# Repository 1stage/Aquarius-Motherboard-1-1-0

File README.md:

# Aquarius Motherboard 1-1-0
Aquarius Motherboard 1-1-0 - Rev C

by Sean P. Harrington, sph@1stage.com, http://aquarius.1stage.com, Mack Wharton, aquarius@mack.je, http://aquarius.je
 
## Background
In general, the Aquarius hardware is fairly hardy. Few of the parts go bad, and the system just works, even when stored in harsh or unforgiving environments. Add to that the poor reception the computer had during its brief, 3-4 month sales window in 1983, and there is no REAL reason most people would be interested. But the Mattel Aquarius Computer was the first computer I ever owned. I learned first hand how to program in BASIC, and then how to hack together an audio cable to save those programs to my inexpensive Radio Shack cassette player. However I quickly grew out of it's limited functionality and moved on to a Commodore 64, and then an Apple Macintosh SE, and then Mac II, and then various Windows PCs. It wasn't until Summer of 2019 that I started getting back into retro computers, and it was the pang of guilt I felt in abandoning my first Aquarius that brought me back in.

## Purpose
The purpose of this project is to document and recreate the original Aquarius computer motherboard. This is a like-for-like replacement, and should fit in perfectly in place of the old motherboard. This baseline can be used by other enthusiasts (though we are few and far between) as a starting point for creating new modifications to the system, such as adding a composite video adapter (which I've done) to replace the stock RF modulator, or adding more modern components to "future proof" the system.

Additionally, there was a need to update and correct the "MEKO" schematic from 1986. It was drawn from the PAL board, and values for various components seemed to differ from what was commonly manufactured. From these new schematics, users are welcome to adapt and integrate their own ideas, OR to recreate the system in their eCAD program of choice.

## Caveats
* Some fixes to the stock board were made:
  * The .1uF capacitor that was bodged under U6 has been given a proper set of pads beside U6.
  * Silkscreens were added, with all components being identified. Unfortunately, due to the poor quality of original Radofin documents on the Internet, I had to take a stance and perform a re-number of components, particularly resistors and capacitors. In some cases, these won't match original numbers, but every effort was made to get them as close as possible.
  * Both the PAL-only and NTSC-only components are marked, but only the components for the version being built should be used.
  * As much as possible, original trace paths were recreated (particularly CPU to expansion port), but the traces have been reduced to a 20 mil width on most signals, with all GND and power paths increased to 32 mil width.
  * GND pins now have thermal pads to make soldering and desoldering easier.
* The libraries within the Eagle folder are a mess. I apologize. The board uses a combination of the standard Eagle libraries, some copied/modified versions of those, and some of my own items. I'll eventually try to consolidate them into a single library file. Again, apologies.
* This design was taken from the NTSC version of the Aquarius Motherboard, Radofin part number 5931-4229 A. The values for all components are derived from the NTSC version, and where practical, PAL component values are noted on the schematic. As such, the "part number" embossed on these designs uses 5931-4229 AC to differentiate.
* The schematic does it's best to identify differences between the NTSC and PAL versions, usually with dashed lines surrounding the differences.

## FAQs
* Will these boards be available for sale?
  * https://www.pcbway.com/project/shareproject/Aquarius_Computer_Motherboard_v1_1_0_Rev_C.html
* Can I manufacture and sell the boards myself?
  * Sure, but see the section below on why this is more for SERIOUS hackers than casual users.
* Can you build me a new Aquarius with this PCB?
  * No. I have way too many projects at this time. Also, cost of the components ($$) and my time testing and assembling ($$$) would make this MANY times more expensive than buying a used Aquarius off of eBay.
* Can I build my own, brand new Aquarius computer with this PCB?
  * Realistically, no. There are a handful of custom components (bespoke, we like to say) that ONLY exist in the Aquarius computer... the PLA1 and PLA2, some line filters, and a variable inductor... each of which is impractical to source new/NOS. You will HAVE to cannibalize an old Aquarius to get your new Aquarius to work, so given that, you should PROBABLY just use that old Aquarius instead. They're REMARKABLY robust, and the added time and cost of soldering and testing each component on your new board could just as easily be spent learning about your old computer.
* Okay, so then what's the point of this PCB?
  * For futher development to happen to expand the platform, it was necessary to do the work to document the original Aquarius motherboard. From there, people who are interested in adding new components will have a safer, better-documented source from which to start that development. Examples are an RGB or HDMI video interface, incorporated 32Kb of RAM on the motherboard, USB/SD support, etc.
* I don't use Eagle (too expensive), so will you be making this available in KiCAD or some other open-source/free PCB design tool?
  * No, but with the documentation that exists now, feel free to do so yourself. If everyone agrees that your new files work okay, we'll be happy to add them to this project.
* What's next?
  * See the HW Roadmap (below) for our vision.

## Aquarius Hardware Development Roadmap
(A more up-to-date version of this list is at https://aquarius.1stage.com/aquarius/hw-roadmap)

### Aquarius v1.0.0 : Baseline
* Aquarius v1.1.0 (Rev C): Aquarius 1 stock motherboard, like-for-like replacement, SANCTIONED FREE version. 
  * Aquarius v1.1.0.x : Users can fork at this level for their own purposes, UNSANCTIONED versions.
* Aquarius v1.2.0 : Aquarius 1 modernized motherboard, fits in Aquarius 1 case, unmodified port openings may be used differently, SANCTIONED PAID version.
  * Aquarius v1.2.1 : Integrated composite video ???
  * Aquarius v1.2.2 : Modern power supply ???
  * Aquarius v1.2.3 : Charmap, ROM, updates ???
* Aquarius v1.3.0 : Aquarius 1 motherboard, new layout, new case format, etc. ???
  * Aquarius v1.3.1 : New case design with mechanical keyboard, RGB output, proper serial, etc. ???

### Aquarius v2.0.0 : Baseline (FUTURE)
* Aquarius v2.1.0 : Aquarius 2 stock motherboard, like-for-like replacement, SANCTIONED FREE version.
  * Aquarius v2.1.0.x : Users can fork at this level for their own purposes, UNSANCTIONED versions.
  * Aquarius v2.1.1 : Aquarius 2 motherboard, updated with proper silk screen markings and ground planes, SANCTIONED PAID version.
  * Aquarius v2.1.2 : Aquarius 2 motherboard, updated with bodge fixes, modern component replacements, traces may be updated/optimized, SANCTIONED PAID version.
* Aquarius v2.2.0 : Aquarius 2 modernized motherboard, fits in Aquarius 2 case, unmodified port openings may be used differently, SANCTIONED PAID version.
  * Aquarius v2.2.1 : Charmap, ROM, etc updates ???
* Aquarius v2.3.0 : Aquarius 2 motherboard, new layout, new case format, etc. ???

### Aquarius v3.0.0 : Baseline (FUTURE)
New OPEN computer, modern, programmable system (new video system, RAM system, sound, etc.)
* Aquarius v3.1.0 : Aquarius 3 motherboard, SANCTIONED FREE version

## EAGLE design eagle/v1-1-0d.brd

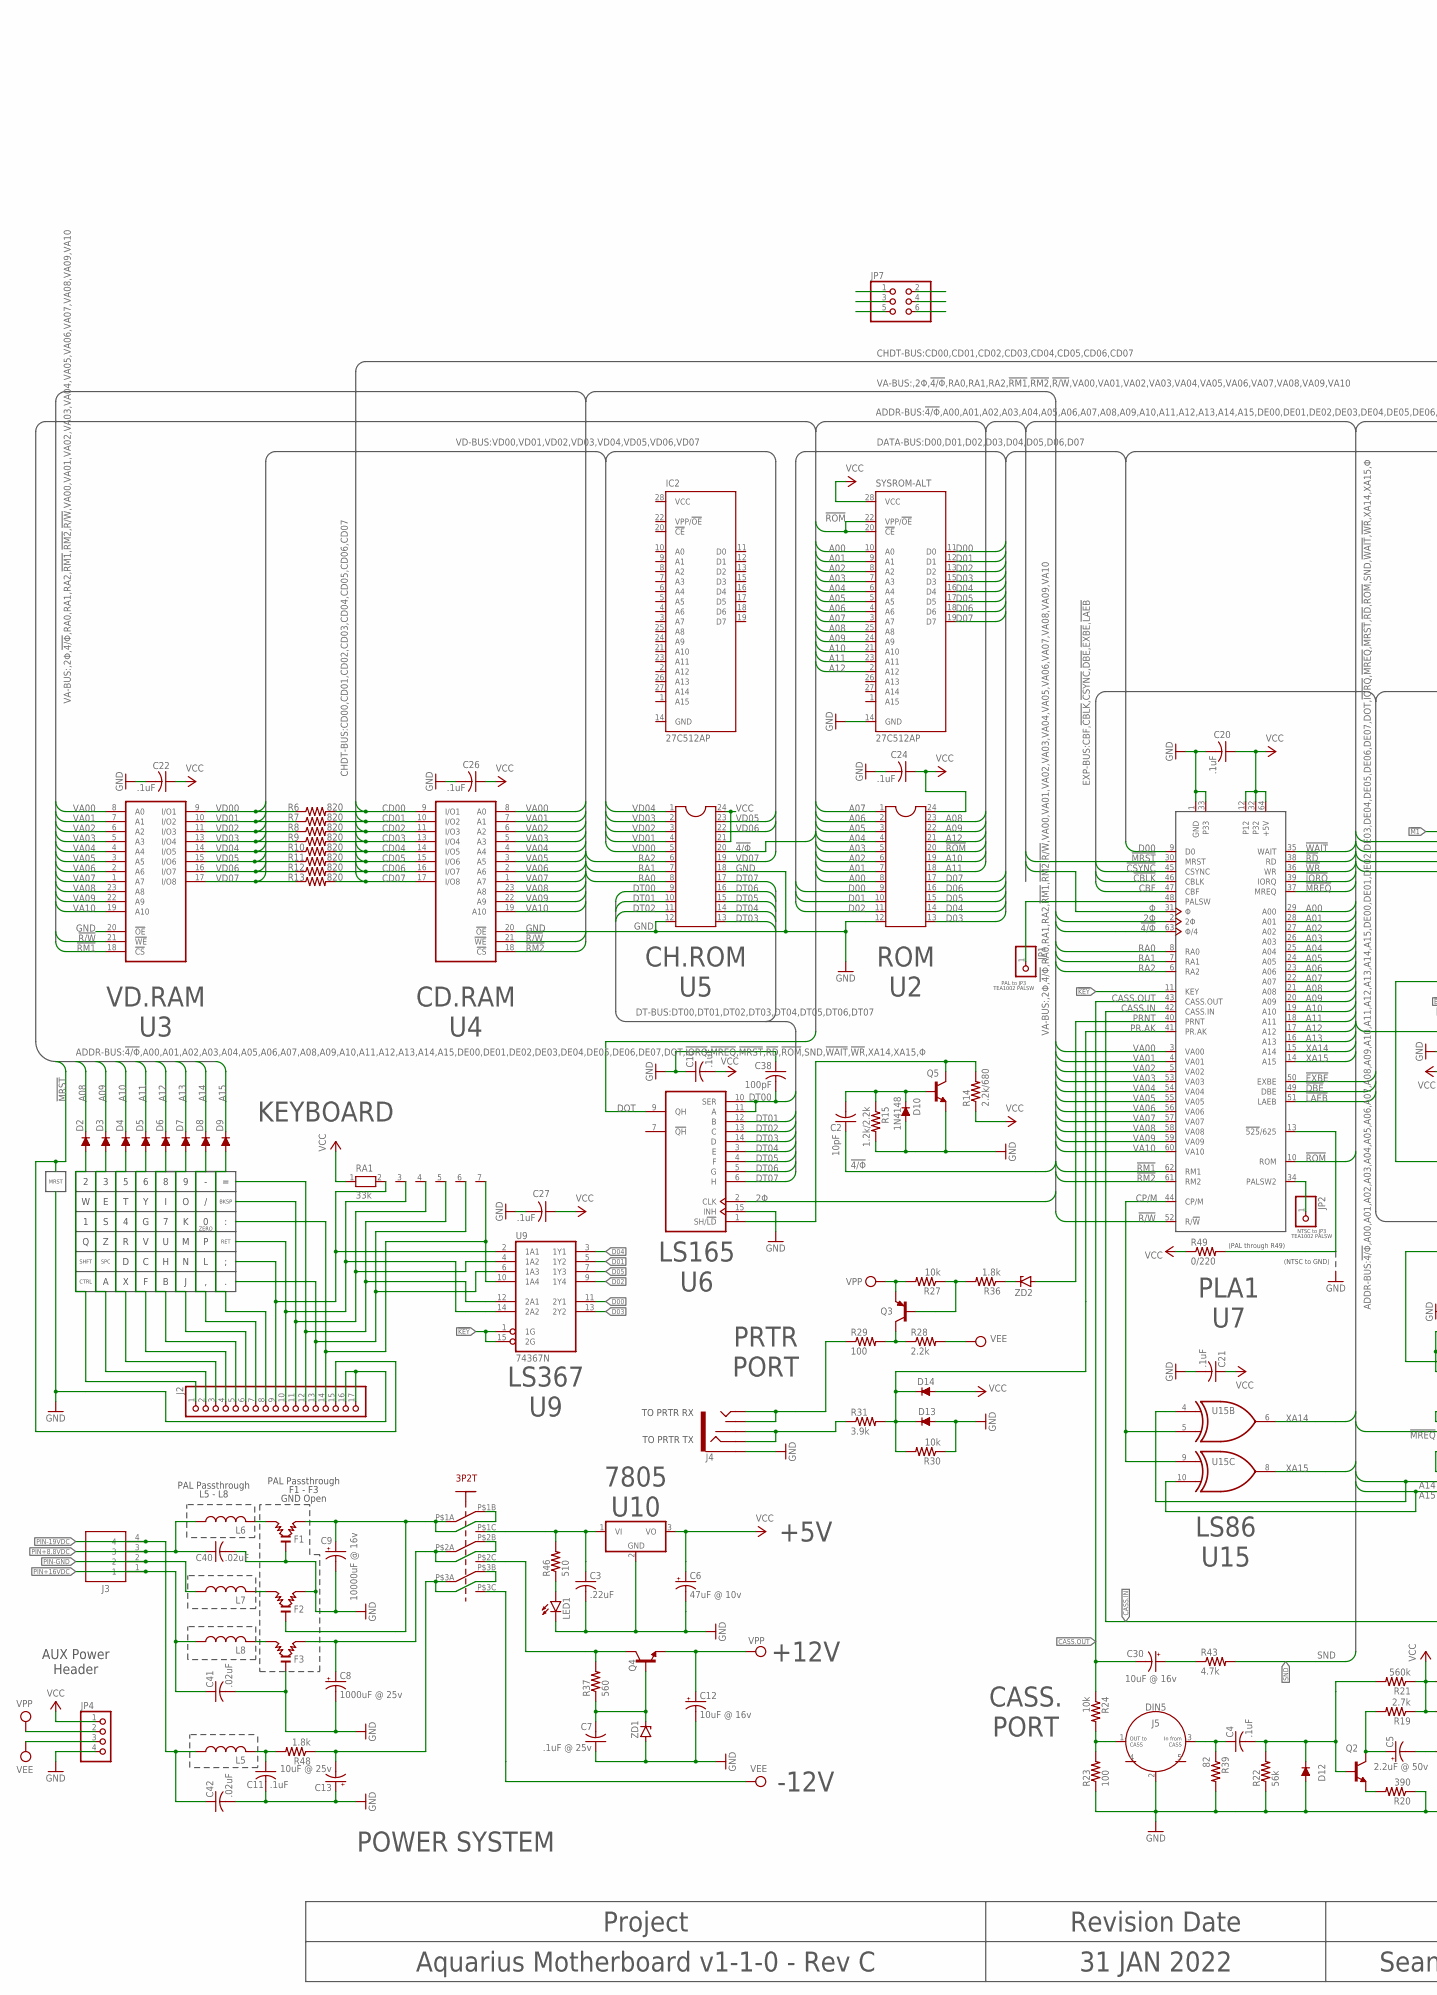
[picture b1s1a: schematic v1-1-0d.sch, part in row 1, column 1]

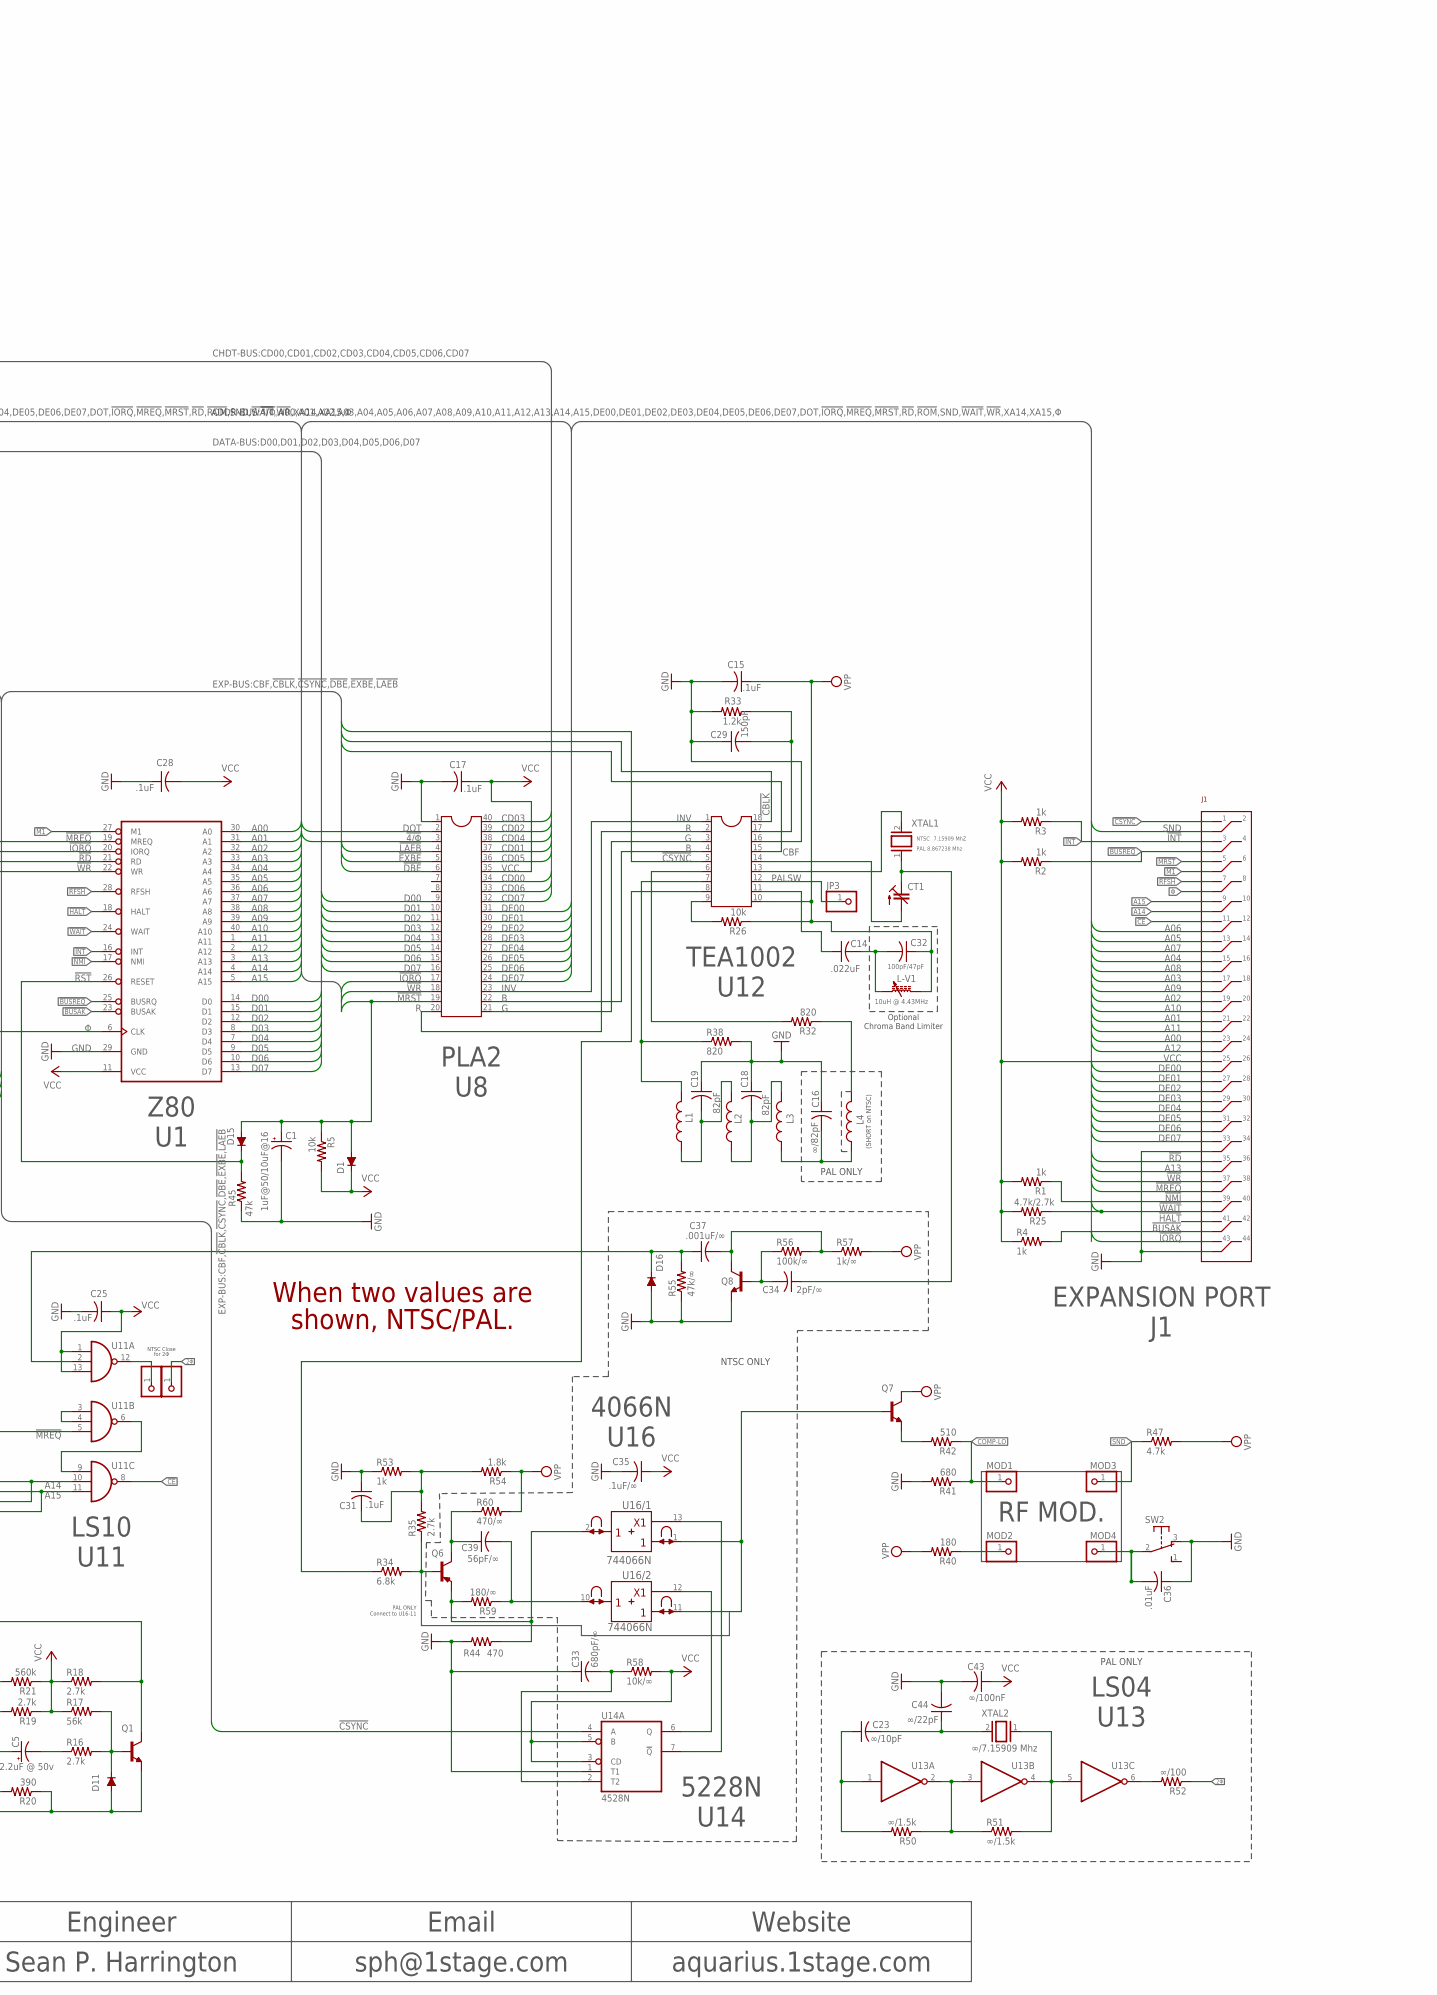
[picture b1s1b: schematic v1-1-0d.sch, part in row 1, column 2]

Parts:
C1: 1uF@50/10uF@16; E2,5-6
C2: 10pF; C050-024X044
C3: .22uF; C050-025X090
C4, C10, C11, C15, C17, C20, C21, C24, C25, C27, C28: .1uF; C050-025X090
C5: 2.2uF @ 50v; E2,5-6
C6: 47uF @ 10v; E2,5-6
C7: .1uF @ 25v; C050-025X090
C8: 1000uF @ 25v; E7,5-16
C9: 10000uF @ 16v; E45-18
C12, C30: 10uF @ 16v; E2,5-6
C13: 10uF @ 25v; E2,5-6
C14: .022uF; C050-024X044
C16: ∞/82pF; C050-024X044
C18, C19: 82pF; C050-024X044
C22, C26: .1uF; C050-025X085
C23: ∞/10pF; C050-024X044
C29: 150pF; C050-024X044
C31: .1uF; C050-024X044
C32: 100pF/47pF; C025-024X044
C33: 680pF/∞; C050-024X044
C34: 2pF/∞; C025-024X044
C35: .1uF/∞; C050-025X090
C36: .01uF; C050-024X044
C37: .001uF/∞; C025-030X050
C38: 100pF; C050-025X085
C39: 56pF/∞; C050-024X044
C40, C41, C42: .02uF; C050-025X090
C43: ∞/100nF; C050-025X090
C44: ∞/22pF; C050-024X044
CT1: C-TRIMM808; CTRIM808-BC
D1, D10, D11, D12, D13, D14, D15, D16: 1N4148; DO35-10
D2, D3, D4, D5, D6, D7, D8, D9: 1N4148H; DO35-12
F1, F2, F3: LCL
IC2: 27C512AP; DIL28-6
J1: CR22A-44D-2.54DSA(70)
J2: PINHD-1X17; 1X17
J3: 26-60-4040; SHDR4W155P0X396_1X4_1570X1001X
J4: AUDIO_JACK_3.5MM_PTH; AUDIO-JACK
J5: DIN5; DIN5-RA-PTH
JP1, JP2, JP3, JP5, JP6: PINHD-1X1; 1X01
JP4: PINHD-1X4; 1X04
JP7: PINHD-2X3; 2X03
L1, L2, L3, L4, L5, L6, L7, L8: L-USTFI0305; TFI0305
L-V1: 10uH @ 4.43MHz; 10MM-VAR-IND
LED1: LED5MM
MOD1, MOD2, MOD3, MOD4: PINHD-1X1; 1X01
Q1, Q2, Q5, Q7, Q8: -NPN-TO92-E1; TO92-E1
Q3, Q6: -PNP-TO92-E1; TO92-E1
Q4: -NPN-TO220V; TO220V
R1, R2, R3, R4, R53: 1k; 0207/10
R5, R24, R26, R27, R30: 10k; 0207/10
R6, R7, R8, R9, R10, R11, R12, R13, R32, R38: 820; 0207/10
R14: 2.2k/680; 0207/10
R15: 1.2k/2.2k; 0207/10
R16, R18, R19, R35: 2.7k; 0207/10
R17, R22: 56k; 0207/10
R20: 390; 0207/10
R21: 560k; 0207/10
R23, R29: 100; 0207/10
R25: 4.7k/2.7k; 0207/10
R28: 2.2k; 0207/10
R31: 3.9k; 0207/10
R33: 1.2k; 0207/10
R34: 6.8k; 0207/10
R36, R48, R54: 1.8k; 0207/10
R37: 560; 0207/10
R39: 82; 0207/10
R40: 180; 0207/10
R41: 680; 0207/10
R42, R46: 510; 0207/10
R43, R47: 4.7k; 0207/10
R44: 470; 0207/10
R45: 47k; 0207/10
R49: 0/220; 0207/10
R50, R51: ∞/1.5k; 0207/10
R52: ∞/100; 0207/10
R55: 47k/∞; 0207/10
R56: 100k/∞; 0207/10
R57: 1k/∞; 0207/10
R58: 10k/∞; 0207/10
R59: 180/∞; 0207/10
R60: 470/∞; 0207/10
RA1: 33k; RN-7
SW1: 3PDT-AQ-SWITCH
SW2: 9077-1
SYSROM-ALT: 27C512AP; DIL28-6
U1: Z80CPU; DIL40
U2, U5: DIL24-6
U3, U4: 6116P; DIL24-6
U6: 74LS165N; DIL16
U7: HD61K202P-PLA1
U8: DIL40
U9: 74367N; DIL16
U10: 7805; TO220V
U11: 74LS10N; DIL14
U12: DIL18
U13: 74LS04N; DIL14
U14: 4528N; DIL16
U15: 74LS86N; DIL14
U16: 744066N; DIL14
XTAL1: 7.15909 MhZ; Q
XTAL2: ∞/7.15909 Mhz; Q
ZD1: ZENER-DIODEZD-10; ZDIO-10
ZD2: ZENER-DIODEZD-7.5; ZDIO-7.5

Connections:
2Φ: JP6.1, R52.1, U6.2 (CLK), U7.2 (2Φ)
2Φ-NTSC: JP5.1, U11.12 (O)
!4/Φ: C2.1, U5.20, U7.63 (Φ/4), U8.3
!BUSAK: J1.P$42 (X42), R4.2, U1.23 (BUSAK)
!BUSREQ: J1.P$4 (X4), R2.1, U1.25 (BUSRQ)
!CBLK: U7.46 (CBLK), U12.18
!CE: J1.P$11 (X11), U11.8 (O)
!CSYNC: J1.P$1 (X1), U7.45 (CSYNC), U12.5, U14.4 (A)
!DBE: U7.49 (DBE), U8.6
!EXBE: U7.50 (EXBE), U8.5
!HALT: J1.P$41 (X41), U1.18 (HALT)
!INT: J1.P$3 (X3), R3.1, U1.16 (INT)
!IORQ: J1.P$43 (X43), U1.20 (IORQ), U7.39 (IORQ), U8.17
!KEY: U7.11 (KEY), U9.1 (1G), U9.15 (2G)
!LAEB: U7.51 (LAEB), U8.4
!M1: J1.P$6 (X6), U1.27 (M1)
!MREQ: J1.P$38 (X38), U1.19 (MREQ), U7.37 (MREQ), U11.5 (I2)
!MRST: C1.+, D1.A, D15.A, J1.P$5 (X5), J2.15, R5.1, U7.30 (MRST), U8.19
!NMI: J1.P$39 (X39), R1.1, U1.17 (NMI)
!PL: Q5.1 (C), R14.2, U6.1 (SH/!LD)
!R/W: U3.21 (!WE), U4.21 (!WE), U7.52 (R/!W)
!RD: J1.P$35 (X35), U1.21 (RD), U7.38 (RD)
!RFSH: J1.P$7 (X7), U1.28 (RFSH)
!RM1: U3.18 (!CS), U7.62 (RM1)
!RM2: U4.18 (!CS), U7.61 (RM2)
!ROM: SYSROM-ALT.20 (!CE), SYSROM-ALT.22 (VPP/!OE), U2.20, U7.10 (ROM)
!RST: D15.C, R45.2, U1.26 (RESET)
!WAIT: J1.P$40 (X40), R25.1, U1.24 (WAIT), U7.35 (WAIT)
!WR: J1.P$37 (X37), U1.22 (WR), U7.36 (WR), U8.18
A00: J1.P$23 (X23), SYSROM-ALT.10 (A0), U1.30 (A0), U2.8, U7.29 (A00)
A01: J1.P$21 (X21), SYSROM-ALT.9 (A1), U1.31 (A1), U2.7, U7.28 (A01)
A02: J1.P$19 (X19), SYSROM-ALT.8 (A2), U1.32 (A2), U2.6, U7.27 (A02)
A03: J1.P$17 (X17), SYSROM-ALT.7 (A3), U1.33 (A3), U2.5, U7.26 (A03)
A04: J1.P$15 (X15), SYSROM-ALT.6 (A4), U1.34 (A4), U2.4, U7.25 (A04)
A05: J1.P$13 (X13), SYSROM-ALT.5 (A5), U1.35 (A5), U2.3, U7.24 (A05)
A06: J1.P$12 (X12), SYSROM-ALT.4 (A6), U1.36 (A6), U2.2, U7.23 (A06)
A07: J1.P$14 (X14), SYSROM-ALT.3 (A7), U1.37 (A7), U2.1, U7.22 (A07)
A08: D2.C, J1.P$16 (X16), SYSROM-ALT.25 (A8), U1.38 (A8), U2.23, U7.21 (A08)
A09: D3.C, J1.P$18 (X18), SYSROM-ALT.24 (A9), U1.39 (A9), U2.22, U7.20 (A09)
A10: D4.C, J1.P$20 (X20), SYSROM-ALT.21 (A10), U1.40 (A10), U2.19, U7.19 (A10)
A11: D5.C, J1.P$22 (X22), SYSROM-ALT.23 (A11), U1.1 (A11), U2.18, U7.18 (A11)
A12: D6.C, J1.P$24 (X24), SYSROM-ALT.2 (A12), U1.2 (A12), U2.21, U7.17 (A12)
A13: D7.C, J1.P$36 (X36), U1.3 (A13), U7.16 (A13)
A14: D8.C, J1.P$10 (X10), U1.4 (A14), U11.10 (I1), U15.4 (I0)
A15: D9.C, J1.P$9 (X9), U1.5 (A15), U11.11 (I2), U15.10 (I1)
B: U8.22, U12.4
CASS.IN: Q1.1 (C), R18.2, U7.42 (CASS.IN)
CASS.OUT: C30.-, R24.1, U7.43 (CASS.OUT)
CBF: U7.47 (CBF), U12.15
CD00: R6.2, U4.9 (I/O1), U8.34
CD01: R7.2, U4.10 (I/O2), U8.37
CD02: R8.2, U4.11 (I/O3), U8.39
CD03: R9.2, U4.13 (I/O4), U8.40
CD04: R10.2, U4.14 (I/O5), U8.38
CD05: R11.2, U4.15 (I/O6), U8.36
CD06: R12.2, U4.16 (I/O7), U8.33
CD07: R13.2, U4.17 (I/O8), U8.32
COMP-LO: MOD1.1, R41.1, R42.1
CP/M: U7.44 (CP/M), U15.5 (I1), U15.9 (I0)
D00: SYSROM-ALT.11 (D0), U1.14 (D0), U2.9, U7.9 (D0), U8.9, U9.11 (2Y1)
D01: SYSROM-ALT.12 (D1), U1.15 (D1), U2.10, U8.10, U9.5 (1Y2)
D02: SYSROM-ALT.13 (D2), U1.12 (D2), U2.11, U8.11, U9.9 (1Y4)
D03: SYSROM-ALT.15 (D3), U1.8 (D3), U2.13, U8.12, U9.13 (2Y2)
D04: SYSROM-ALT.16 (D4), U1.7 (D4), U2.14, U8.13, U9.3 (1Y1)
D05: SYSROM-ALT.17 (D5), U1.9 (D5), U2.15, U8.14, U9.7 (1Y3)
D06: SYSROM-ALT.18 (D6), U1.10 (D6), U2.16, U8.15
D07: SYSROM-ALT.19 (D7), U1.13 (D7), U2.17, U8.16
DE00: J1.P$26 (X26), U8.31
DE01: J1.P$27 (X27), U8.30
DE02: J1.P$28 (X28), U8.29
DE03: J1.P$29 (X29), U8.28
DE04: J1.P$30 (X30), U8.27
DE05: J1.P$31 (X31), U8.26
DE06: J1.P$32 (X32), U8.25
DE07: J1.P$33 (X33), U8.24
DOT: U6.9 (QH), U8.2
DT00: C38.2, U5.9, U6.10 (SER), U6.11 (A)
DT01: U5.10, U6.12 (B)
DT02: U5.11, U6.13 (C)
DT03: U5.13, U6.14 (D)
DT04: U5.14, U6.3 (E)
DT05: U5.15, U6.4 (F)
DT06: U5.16, U6.5 (G)
DT07: U5.17, U6.6 (H)
G: U8.21, U12.3
INV: U8.23, U12.1
KH01: D2.A, J2.1
KH02: D3.A, J2.2
KH03: D4.A, J2.3
KH04: D5.A, J2.4
KH05: D6.A, J2.5
KH06: D7.A, J2.6
KH07: D8.A, J2.7
KH08: D9.A, J2.8
KH09: J2.9, RA1.2, U9.2 (1A1)
KH10: J2.10, RA1.3, U9.14 (2A2)
KH11: J2.11, RA1.4, U9.4 (1A2)
KH12: J2.12, RA1.5, U9.12 (2A1)
KH13: J2.13, RA1.6, U9.6 (1A3)
KH14: J2.14, RA1.7, U9.10 (1A4)
unnamed: R49.2, U7.13 (!525!/625)
unnamed: U11.3 (I0), U11.4 (I1)
unnamed: JP2.1, U7.34 (PALSW2)
unnamed: U11.6 (O), U11.9 (I0)
unnamed: C29.2, R33.1, U12.17
unnamed: C5.+, Q2.1 (C), R19.2
unnamed: C4.2, D12.C, Q2.2 (B), R21.2, R22.2
unnamed: Q2.3 (E), R20.2
unnamed: C9.+, F1.2, F2.0 (GND), SW1.P$1A, SW1.P$1B
unnamed: C13.-, R48.1, SW1.P$3A, SW1.P$3B
unnamed: J4.TIP, J4.TSH, R29.1
unnamed: Q6.2 (B), R34.2, R35.1
unnamed: C3.1, R46.2, SW1.P$1C, U10.1 (VI)
unnamed: Q4.2 (C), R37.2, SW1.P$2C
unnamed: C16.2, L3.1, L4.1
unnamed: C19.2, L1.1, L2.2
unnamed: C2.2, D10.C, Q5.2 (B), R15.1
unnamed: F3.1, L8.2
unnamed: R26.2, U12.9
unnamed: C31.2, R35.2, R53.2, R54.2
unnamed: C18.2, L2.1, L3.2
unnamed: Q3.1 (C), R28.1, R29.2
unnamed: L4.2, R32.1
unnamed: C34.1, CT1.1 (E), XTAL1.1
unnamed: CT1.2 (A), U12.14
unnamed: R32.2, U12.6
unnamed: L1.2, R38.1, U12.7
unnamed: U12.13, XTAL1.2
unnamed: U14.6 (Q), U16.12 (C)
unnamed: J5.1, R23.2, R24.2
unnamed: Q7.3 (E), R42.2
unnamed: C30.+, R43.1
unnamed: C14.1, U12.11
unnamed: Q3.2 (B), R27.1, R36.2
unnamed: R34.1, U12.8
unnamed: C36.2, MOD4.1, SW2.2
unnamed: C4.1, J5.3, R39.1
unnamed: C37.1, D16.C, R55.2, U11.2 (I1)
unnamed: Q6.3 (E), R44.1, R59.2, U16.2 (B)
unnamed: JP1.1, U7.48 (PALSW)
unnamed: C33.2, R58.1, U14.2 (T2)
unnamed: C37.2, Q8.1 (C), R56.2, R57.1
unnamed: Q7.2 (B), U16.1 (A), U16.11 (A)
unnamed: LED1.A, R46.1
unnamed: R52.2, U13.6 (O)
unnamed: C7.2, Q4.1 (B), R37.1, ZD1.C
unnamed: D11.C, Q1.2 (B), R16.2, R17.2
unnamed: R36.1, ZD2.C
unnamed: C39.1, Q6.1 (C), R60.1
unnamed: J4.RING, J4.RSH, R31.1
unnamed: U14.7 (!Q), U16.13 (C)
unnamed: R50.1, R51.1, U13.2 (O), U13.3 (I)
unnamed: C23.1, R50.2, U13.1 (I)
unnamed: C39.2, R59.1, U16.10 (B)
unnamed: R51.2, U13.4 (O), U13.5 (I), XTAL2.1
unnamed: C23.2, C44.1, XTAL2.2
unnamed: F2.1, L7.2
unnamed: C34.2, Q8.2 (B), R56.1
unnamed: C8.+, F3.2, SW1.P$2A, SW1.P$2B
unnamed: F1.1, L6.2
unnamed: C11.1, L5.2, R48.2
unnamed: MOD2.1, R40.1
unnamed: C14.2, C32.2, L-V1.P$1, L-V1.P$3
unnamed: C5.-, R16.1
PALSW: JP3.1, U12.12
PIN+8.8VDC: C40.1, J3.3, L6.1
PIN+16VDC: C41.1, J3.1, L8.1
PIN-19VDC: C42.1, J3.4, L5.1
PIN-GND: J3.2, L7.1
PR.AK: D13.C, D14.C, R30.2, R31.2, U7.41 (PR.AK)
PRNT: U7.40 (PRNT), ZD2.A
R: U8.20, U12.2
RA0: U5.8, U7.8 (RA0)
RA1: U5.7, U7.7 (RA1)
RA2: U5.6, U7.6 (RA2)
SND: J1.P$2 (X2), MOD3.1, R43.2, R47.1
VA00: U3.8 (A0), U4.8 (A0), U7.3 (VA00)
VA01: U3.7 (A1), U4.7 (A1), U7.4 (VA01)
VA02: U3.6 (A2), U4.6 (A2), U7.5 (VA02)
VA03: U3.5 (A3), U4.5 (A3), U7.53 (VA03)
VA04: U3.4 (A4), U4.4 (A4), U7.54 (VA04)
VA05: U3.3 (A5), U4.3 (A5), U7.55 (VA05)
VA06: U3.2 (A6), U4.2 (A6), U7.56 (VA06)
VA07: U3.1 (A7), U4.1 (A7), U7.57 (VA07)
VA08: U3.23 (A8), U4.23 (A8), U7.58 (VA08)
VA09: U3.22 (A9), U4.22 (A9), U7.59 (VA09)
VA10: U3.19 (A10), U4.19 (A10), U7.60 (VA10)
VD00: R6.1, U3.9 (I/O1), U5.5
VD01: R7.1, U3.10 (I/O2), U5.4
VD02: R8.1, U3.11 (I/O3), U5.3
VD03: R9.1, U3.13 (I/O4), U5.2
VD04: R10.1, U3.14 (I/O5), U5.1
VD05: R11.1, U3.15 (I/O6), U5.23
VD06: R12.1, U3.16 (I/O7), U5.22
VD07: R13.1, U3.17 (I/O8), U5.19
VEE: JP4.3, R28.2, SW1.P$3C
VPP: C12.+, C15.1, C32.1, JP4.2, L-V1.P$2, L-V1.P$4, Q3.3 (E), Q4.3 (E), Q7.1 (C), R26.1, R27.2, R40.2, R47.2, R54.1, R57.2, R60.2, U12.10
XA14: U7.15 (A14), U15.6 (O)
XA15: U7.14 (A15), U15.8 (O)
Φ: J1.P$8 (X8), U1.6 (CLK), U7.31 (Φ)

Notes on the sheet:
Z80 U1
PLA1 U7
PLA2 U8
TEA1002 U12
EXPANSION PORT J1
ROM U2
CH.ROM U5
CD.RAM U4
VD.RAM U3
LS165 U6
LS367 U9
SHFT
CTRL
BKSP
SPC
RET
ZERO
MRST
KEYBOARD
POWER SYSTEM
RF MOD.
PAL ONLY
(SHORT on NTSC)
7805 U10
PRTR PORT
CASS. PORT
LS86 U15
LS10 U11
Sean P. Harrington
Engineer
sph@1stage.com
Email
Aquarius Motherboard v1-1-0 - Rev C
Project
31 JAN 2022
Revision Date
Website
aquarius.1stage.com
5228N U14
4066N U16

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
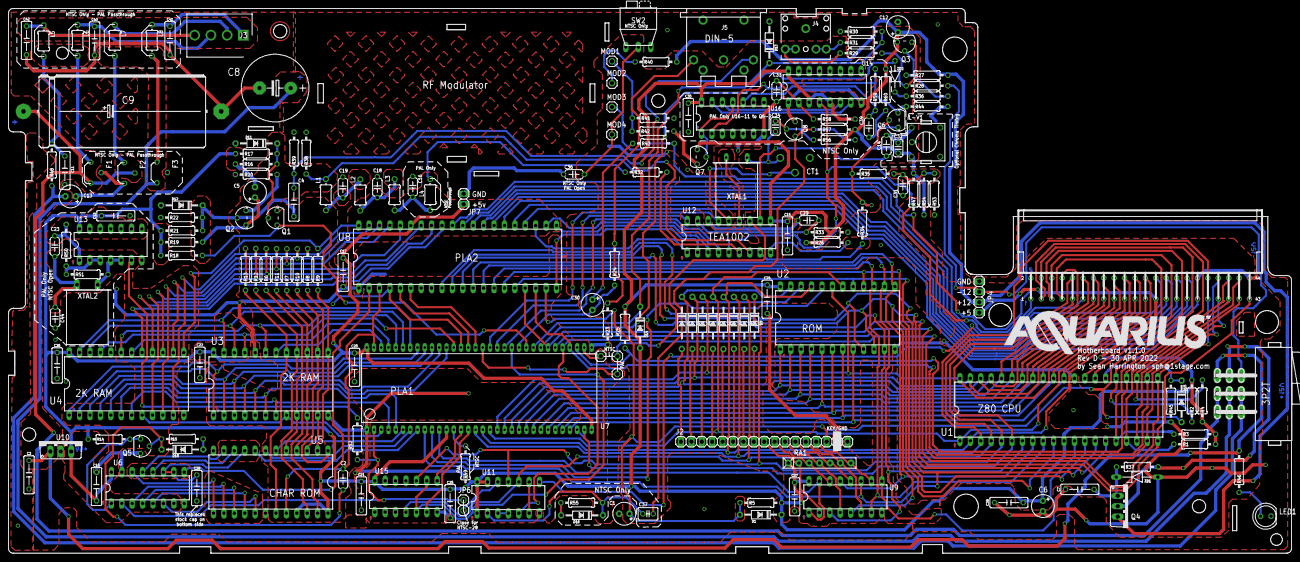
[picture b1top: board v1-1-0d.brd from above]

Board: 2 copper layers, 313.0 x 132.9 mm, 182 parts (1 on the bottom side), 202 nets.

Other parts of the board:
U$1: AQUARIUS-LOGO-SMALL

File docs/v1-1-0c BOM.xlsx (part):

Part | NTSC Value | PAL Value | Device | Package
C1 | 1uF@50 | 10uF@16 | CPOL-USE2.5-6 | E2,5-6
C2 | 10pF | 10pF | C-US050-024X044 | C050-024X044
C3 | .22uF | .22uF | C-US050-025X090 | C050-025X090
C4 | .1uF | .1uF | C-US050-025X090 | C050-025X090
C5 | 2.2uF@50v | 2.2uF@50v | CPOL-USE2.5-6 | E2,5-6
C6 | 47uF@10v | 47uF@10v | CPOL-USE2.5-6 | E2,5-6
C7 | .1uF@25v | .1uF@25v | C-US050-025X090 | C050-025X090
C8 | 1000uF@25v | 1000uF@25v | CPOL-USE7.5-16 | E7,5-16
C9 | 10000uF@16v | 10000uF@16v | CPOL-USE45-18AXIAL | E45-18
C10 | .1uF | .1uF | C-US050-025X090 | C050-025X090
C11 | .1uF | .1uF | C-US050-025X090 | C050-025X090
C12 | 10uF@16v | 10uF@16v | CPOL-USE2.5-6 | E2,5-6
C13 | 10uF@25v | 10uF@25v | CPOL-USE2.5-6 | E2,5-6
C14 | .022uF | .022uF | C-US050-024X044 | C050-024X044
C15 | .1uF | .1uF | C-US050-025X090 | C050-025X090
C16 | open | 82pF | C-US050-024X044 | C050-024X044
C17 | .1uF | .1uF | C-US050-025X090 | C050-025X090
C18 | 82pF | 82pF | C-US050-024X044 | C050-024X044
C19 | 82pF | 82pF | C-US050-024X044 | C050-024X044
C20 | .1uF | .1uF | C-US050-025X090 | C050-025X090
C21 | .1uF | .1uF | C-US050-025X090 | C050-025X090
C22 | .1uF | .1uF | C-US050-025X085 | C050-025X085
C23 | open | 10pF | C-US050-024X044 | C050-024X044
C24 | .1uF | .1uF | C-US050-025X090 | C050-025X090
C25 | .1uF | .1uF | C-US050-025X090 | C050-025X090
C26 | .1uF | .1uF | C-US050-025X085 | C050-025X085
C27 | .1uF | .1uF | C-US050-025X090 | C050-025X090
C28 | .1uF | .1uF | C-US050-025X090 | C050-025X090
C29 | 150pF | 150pF | C-US050-024X044 | C050-024X044
C30 | 10uF@16v | 10uF@16v | CPOL-USE2.5-6 | E2,5-6
C31 | .1uF | .1uF | C-US050-024X044 | C050-024X044
C32 | 100pF | 100pF | C-US025-024X044 | C025-024X044
C33 | 680pF | open | C-US050-024X044 | C050-024X044
C34 | 2pF | open | C-US025-024X044 | C025-024X044
C35 | .1uF | open | C-US050-025X090 | C050-025X090
C36 | .01uF | .01uF | C-US050-024X044 | C050-024X044
C37 | .001uF | open | C-US025-030X050 | C025-030X050
C38 | 100pF | 100pF | C-US050-025X085 | C050-025X085
C39 | 56pF | open | C-US050-024X044 | C050-024X044
C40 | .02uF | .02uF | C-US050-025X090 | C050-025X090
C41 | .02uF | .02uF | C-US050-025X090 | C050-025X090
C42 | .02uF | .02uF | C-US050-025X090 | C050-025X090
C43 | open | 100nF | C-US050-025X090 | C050-025X090
C44 | open | 22pF | C-US050-024X044 | C050-024X044
CT1 | C-TRIMM808 | C-TRIMM808 | CTRIM808-BC | Trimmcapacitor
D1 | 1N4148 | 1N4148 | 1N4148 | DO35-10
D2 | 1N4148H | 1N4148H | 1N4148-12 | DO35-12
D3 | 1N4148H | 1N4148H | 1N4148-12 | DO35-12
D4 | 1N4148H | 1N4148H | 1N4148-12 | DO35-12
D5 | 1N4148H | 1N4148H | 1N4148-12 | DO35-12
D6 | 1N4148H | 1N4148H | 1N4148-12 | DO35-12
D7 | 1N4148H | 1N4148H | 1N4148-12 | DO35-12
D8 | 1N4148H | 1N4148H | 1N4148-12 | DO35-12
D9 | 1N4148H | 1N4148H | 1N4148-12 | DO35-12
D10 | 1N4148 | 1N4148 | 1N4148 | DO35-10
D11 | 1N4148 | 1N4148 | 1N4148 | DO35-10
D12 | 1N4148 | 1N4148 | 1N4148 | DO35-10
D13 | 1N4148 | 1N4148 | 1N4148 | DO35-10
D14 | 1N4148 | 1N4148 | 1N4148 | DO35-10
D15 | 1N4148 | 1N4148 | 1N4148 | DO35-10
D16 | 1N4148 | 1N4148 | 1N4148 | DO35-10
F1 | LCL | LCL | LCL | FILTER
F2 | LCL | LCL | LCL | FILTER
F3 | LCL | LCL | LCL | FILTER
J1 | CR22A-44D-2.54DSA(70)CR22A-44D-2.54DSA(70)CR22A-44D-2.54DSA(70) | CR22A-44D-2.54DSA(70)CR22A-44D-2.54DSA(70)CR22A-44D-2.54DSA(70)
J2 | PINHD-1X17 | PINHD-1X17 | 1X17 | PINHEADER
J3 | 26-60-4040 | 26-60-4040 | 26-60-4040 | SHDR4W155P0X396_1X4_
J4 | AUDIO_JACK_3.5MM_PTH | AUDIO_JACK_3.5MM_PTH | AUDIO_JACK_3.5MM_PTH | AUDIO-JACK
J5 | DIN5 | DIN5 | DIN5 | DIN5-RA-PTH
JP1 | PINHD-1X1 | PINHD-1X1 | 1X01 | PINHEADER
JP2 | PINHD-1X1 | PINHD-1X1 | 1X01 | PINHEADER
JP3 | PINHD-1X1 | PINHD-1X1 | 1X01 | PINHEADER
JP4 | PINHD-1X4 | PINHD-1X4 | 1X04 | PINHEADER
JP5 | PINHD-1X1 | PINHD-1X1 | 1X01 | PINHEADER
JP6 | PINHD-1X1 | PINHD-1X1 | 1X01 | PINHEADER
L-V1 | 10uH@4.43MHz | 10uH@4.43MHz | 10MM-VAR-IND | CL2054-136CB
L1 | L-USTFI0305 | L-USTFI0305 | TFI0305 | INDUCTOR,Americansymbol
L2 | L-USTFI0305 | L-USTFI0305 | TFI0305 | INDUCTOR,Americansymbol
L3 | L-USTFI0305 | L-USTFI0305 | TFI0305 | INDUCTOR,Americansymbol
L4 | L-USTFI0305 | L-USTFI0305 | TFI0305 | INDUCTOR,Americansymbol
L5 | L-USTFI0305 | L-USTFI0305 | TFI0305 | INDUCTOR,Americansymbol
L6 | L-USTFI0305 | L-USTFI0305 | TFI0305 | INDUCTOR,Americansymbol
L7 | L-USTFI0305 | L-USTFI0305 | TFI0305 | INDUCTOR,Americansymbol
L8 | L-USTFI0305 | L-USTFI0305 | TFI0305 | INDUCTOR,Americansymbol
LED1 | LED5MM | LED5MM | LED5MM | LED
MOD1 | PINHD-1X1 | PINHD-1X1 | 1X01 | PINHEADER
MOD2 | PINHD-1X1 | PINHD-1X1 | 1X01 | PINHEADER
MOD3 | PINHD-1X1 | PINHD-1X1 | 1X01 | PINHEADER
MOD4 | PINHD-1X1 | PINHD-1X1 | 1X01 | PINHEADER
Q1 | NPN-TO90 | NPN-TO90 | TO92-E1 | NPNTransistror
Q2 | NPN-TO90 | NPN-TO90 | TO92-E1 | NPNTransistror
Q3 | PNP-TO90 | PNP-TO90 | TO92-E1 | PNPTransistror
Q4 | NPN-TO220V | NPN-TO220V | TO220V | NPNTransistror
Q5 | NPN-TO90 | NPN-TO90 | TO92-E1 | NPNTransistror
Q6 | PNP-TO90 | PNP-TO90 | TO92-E1 | PNPTransistror
Q7 | NPN-TO90 | NPN-TO90 | TO92-E1 | NPNTransistror
Q8 | NPN-TO90 | NPN-TO90 | TO92-E1 | NPNTransistror
R1 | 1k | 1k | R-US_0207/10 | 0207/10
R2 | 1k | 1k | R-US_0207/10 | 0207/10
R3 | 1k | 1k | R-US_0207/10 | 0207/10
R4 | 1k | 1k | R-US_0207/10 | 0207/10
R5 | 10k | 10k | R-US_0207/10 | 0207/10
R6 | 820 | 820 | R-US_0207/10 | 0207/10
R7 | 820 | 820 | R-US_0207/10 | 0207/10
R8 | 820 | 820 | R-US_0207/10 | 0207/10
R9 | 820 | 820 | R-US_0207/10 | 0207/10
R10 | 820 | 820 | R-US_0207/10 | 0207/10
R11 | 820 | 820 | R-US_0207/10 | 0207/10
R12 | 820 | 820 | R-US_0207/10 | 0207/10
R13 | 820 | 820 | R-US_0207/10 | 0207/10
R14 | 2.2k | 680 | R-US_0207/10 | 0207/10
R15 | 1.2k | 2.2k | R-US_0207/10 | 0207/10
R16 | 2.7k | 2.7k | R-US_0207/10 | 0207/10
R17 | 56k | 56k | R-US_0207/10 | 0207/10
R18 | 2.7k | 2.7k | R-US_0207/10 | 0207/10
R19 | 2.7k | 2.7k | R-US_0207/10 | 0207/10
R20 | 390k | 390k | R-US_0207/10 | 0207/10
R21 | 560k | 560k | R-US_0207/10 | 0207/10
R22 | 56k | 56k | R-US_0207/10 | 0207/10
R23 | 100 | 100 | R-US_0207/10 | 0207/10
R24 | 10k | 10k | R-US_0207/10 | 0207/10
R25 | 4.7k | 2.7k | R-US_0207/10 | 0207/10
R26 | 10k | 10k | R-US_0207/10 | 0207/10
R27 | 10k | 10k | R-US_0207/10 | 0207/10
R28 | 2.2k | 2.2k | R-US_0207/10 | 0207/10
R29 | 100 | 100 | R-US_0207/10 | 0207/10
R30 | 10k | 10k | R-US_0207/10 | 0207/10
R31 | 3.9k | 3.9k | R-US_0207/10 | 0207/10
R32 | 820 | 820 | R-US_0207/10 | 0207/10
R33 | 1.2k | 1.2k | R-US_0207/10 | 0207/10
R34 | 6.8k | 6.8k | R-US_0207/10 | 0207/10
R35 | 2.7k | 2.7k | R-US_0207/10 | 0207/10
R36 | 1.8k | 1.8k | R-US_0207/10 | 0207/10
R37 | 560 | 560 | R-US_0207/10 | 0207/10
R38 | 820 | 820 | R-US_0207/10 | 0207/10
R39 | 82 | 82 | R-US_0207/10 | 0207/10
R40 | 180 | 180 | R-US_0207/10 | 0207/10
R41 | 680 | 680 | R-US_0207/10 | 0207/10
R42 | 510 | 510 | R-US_0207/10 | 0207/10
R43 | 4.7k | 4.7k | R-US_0207/10 | 0207/10
R44 | 470 | 470 | R-US_0207/10 | 0207/10
R45 | 47k | 47k | R-US_0207/10 | 0207/10
R46 | 510 | 510 | R-US_0207/10 | 0207/10
R47 | 4.7k | 4.7k | R-US_0207/10 | 0207/10
R48 | 1.8k | 1.8k | R-US_0207/10 | 0207/10
R49 | bridge | 220 | R-US_0207/10 | 0207/10
R50 | open | 1.5k | R-US_0207/10 | 0207/10
R51 | open | 1.5k | R-US_0207/10 | 0207/10
R52 | open | 100 | R-US_0207/10 | 0207/10
R53 | 1k | 1k | R-US_0207/10 | 0207/10
R54 | 1.8k | 1.8k | R-US_0207/10 | 0207/10
R55 | 47k | open | R-US_0207/10 | 0207/10
R56 | 100k | open | R-US_0207/10 | 0207/10
R57 | 1k | open | R-US_0207/10 | 0207/10
R58 | 10k | open | R-US_0207/10 | 0207/10
R59 | 180 | open | R-US_0207/10 | 0207/10
R60 | 470 | open | R-US_0207/10 | 0207/10
RA1 | 33k | 33k | RN06 | RN-7
SW1 | 3PDT-AQ-SWITCH | 3PDT-AQ-SWITCH | 3PDT-AQ-SWITCH | 3PDT-AQ-SWITCH
SW2 | 9077-1 | 9077-1 | 9077-1 | 9077-1
U1 | Z80CPU | Z80CPU | DIL40 | Z80FAMILYDEVICE
U2 | DIL24-6 | DIL24-6 | DIL24-6 | DualInLine
U3 | 6116P | 6116P | DIL24-6 | MEMORY
U4 | 6116P | 6116P | DIL24-6 | MEMORY
U5 | DIL24-6 | DIL24-6 | DIL24-6 | DualInLine
U6 | 74LS165N | 74LS165N | 74LS165N | DIL16
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
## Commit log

2020-08-10 First publish
    First publish of the Aquarius Motherboard v1-1-0 rev B
2020-08-18 Edits/corrections from peer feedback.
    Corrected schematic reference to 526 (should be 625) in PLA.
    Put ALL chip signal labels ABOVE signal lines for consistency.
2020-08-18 Schematic and Board updates
2020-08-19 8/19/2020 updates
2020-08-19 Remove Gerber job files
2020-08-19 Edits for component values
2020-08-20 Rev C created
    Thermal trace increases
    Value label clarifications/corrections
    Spacing corrections
2020-08-20 Tweaks
2020-08-20 Housekeeping
2020-08-30 Updated NTSC-only areas on BOARD and SCHEMATIC
2020-08-30 Clean up of values from MW input
2020-08-30 again
2020-09-09 Fix gitignore
2020-10-18 Moved errata to docs and changed to md file
2020-10-19 Errata updates to BRD and SCH and PDFs
2020-10-19 19 OCT 2020 fixes from Errata
2020-10-21 Clean up
2020-10-21 Directed errata to REV-B errata
    Since we're still troubleshooting RevB boards, deliniated errata to more correctly indicate that IT'S the board we're reviewing, even though it's the previous version from what's prominent in the fol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
2020-10-21 Fixed problem with floating pin 15 on U6
2020-11-06 XTAL Boost cap added
2020-12-09 09 DEC Update
2021-01-15 January fixes
2021-01-19 Rev C Full Release
2021-01-19 Added social media images
2021-01-19 Clean-up, post go live
2021-02-02 Tweaks to BRD and Gerber files for thermals
2021-03-17 Layout update
    Fix a positioning problem with right cartridge port alignment/screw hole.
2021-04-20 Correct input voltages on PSU for schematic
2022-02-01 Fix R20 value and update docs
2022-03-13 Fix R20 values
2022-04-29 Rev D updates
2022-09-29 Edits before 1-2-0

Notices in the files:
parts and their libraries:
SparkFun-Connectors: Licensing: Creative Commons ShareAlike 4.0 International - https://creativecommons.org/licenses/by-sa/4.0
